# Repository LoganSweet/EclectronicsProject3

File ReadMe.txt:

Olin College of Engineering 
Eclectronics Falls 2017

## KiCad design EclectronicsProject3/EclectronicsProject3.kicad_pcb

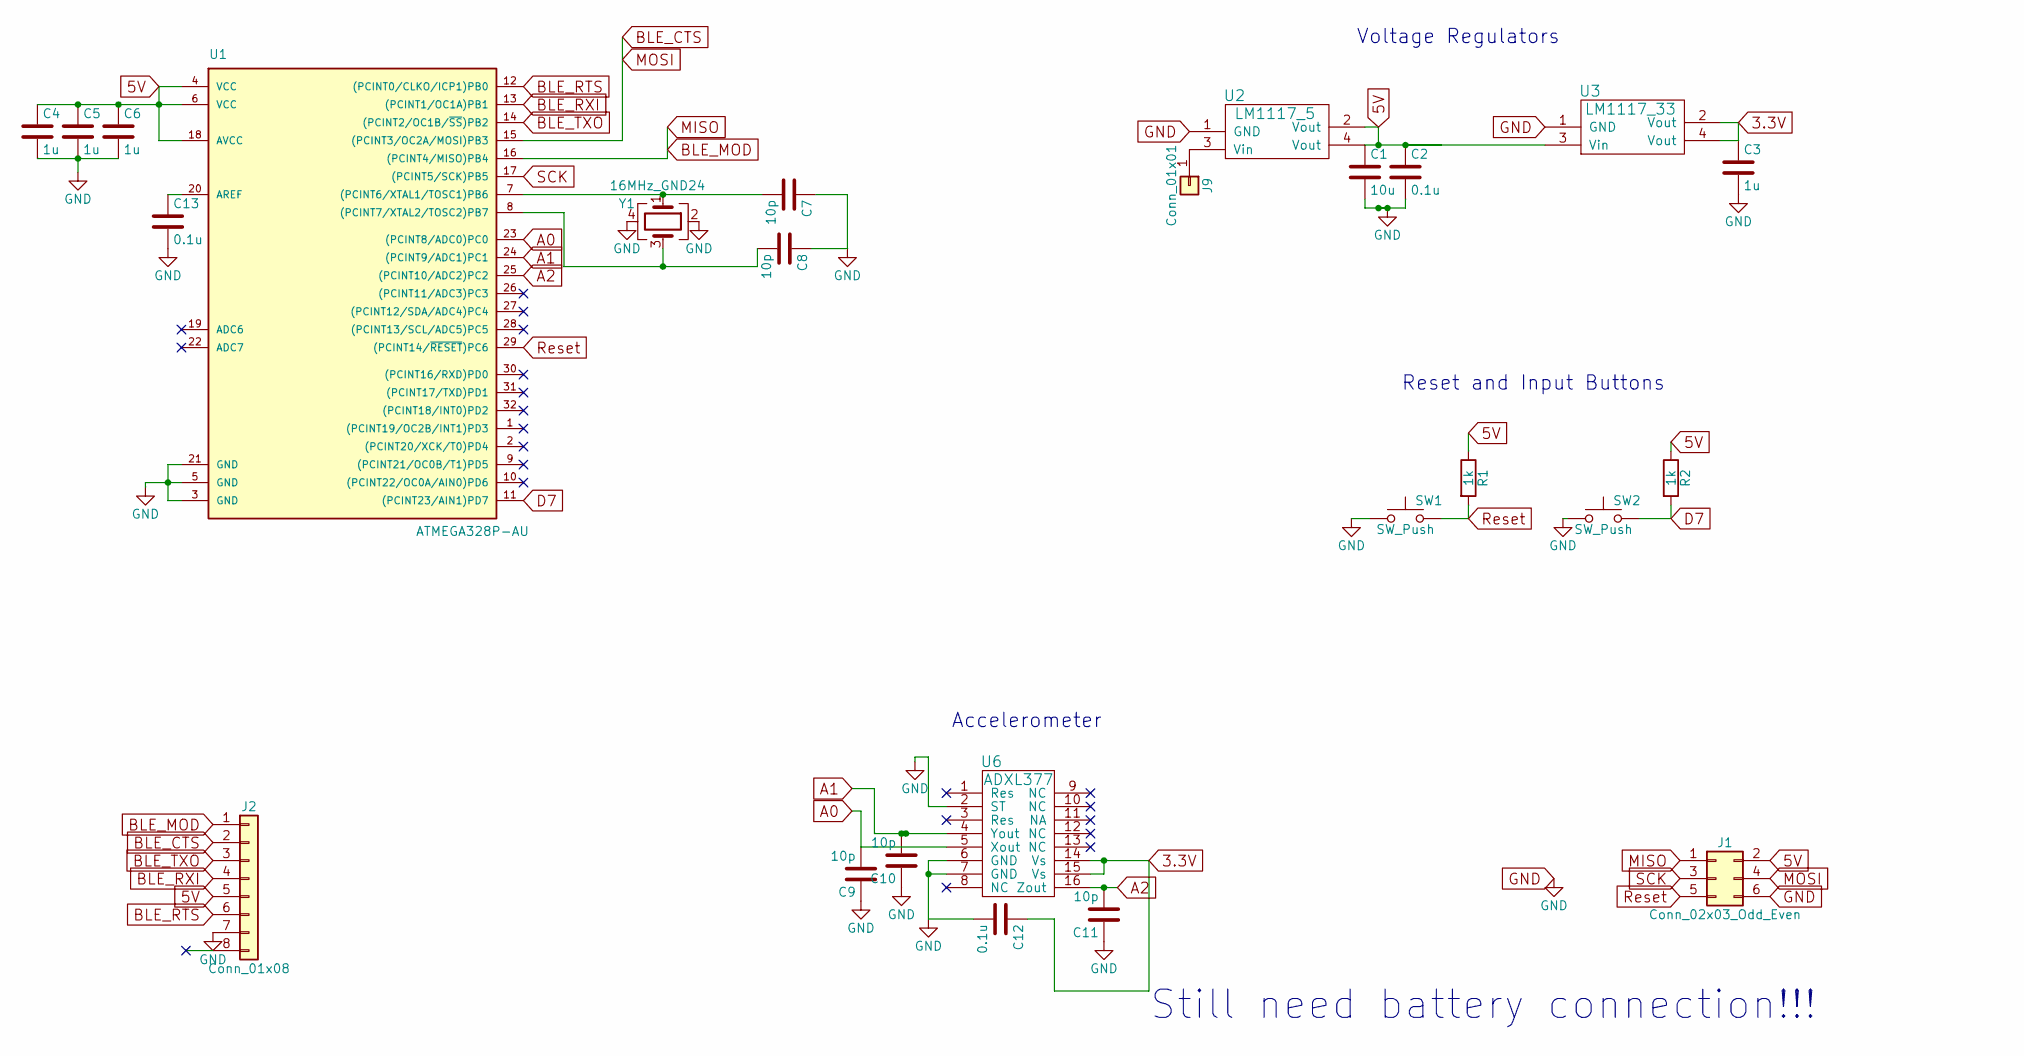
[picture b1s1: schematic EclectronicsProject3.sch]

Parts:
C1: 10u; C_0805
C2, C12, C13: 0.1u; C_0603
C3, C4, C5, C6: 1u; C_0603
C7, C8, C9, C10, C11: 10p; C_0603
J1: Conn_02x03_Odd_Even; Pin_Header_Straight_2x03_Pitch2.54mm
J2: Conn_01x08; Pin_Header_Straight_1x08_Pitch2.54mm
J9: Conn_01x01; Pin_Header_Straight_1x01_Pitch2.54mm
R1, R2: 1k; R_0603
SW1, SW2: SW_Push; SW_SPST_B3U-1000P
U1: ATMEGA328P-AU; TQFP-32_7x7mm_Pitch0.8mm
U2: LM1117_5; SOT-223
U3: LM1117_33; SOT-223
U6: ADXL377; QFN-16-1EP_3x3mm_Pitch0.5mm
Y1: 16MHz_GND24; Crystal_SMD_Abracon_ABM8G-4pin_3.2x2.5mm

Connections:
3.3V: C3.1, C12.1, U3.2 (Vout), U3.4 (Vout), U6.14 (Vs), U6.15 (Vs)
5V: C1.1, C2.1, C4.1, C5.1, C6.1, J1.2, J2.5, R1.1, R2.1, U1.4 (VCC), U1.6 (VCC), U1.18 (AVCC), U2.2 (Vout), U2.4 (Vout), U3.3 (Vin)
A0: C9.2, U1.23 ((PCINT8/ADC0)PC0), U6.5 (Xout)
A1: C10.2, U1.24 ((PCINT9/ADC1)PC1), U6.4 (Yout)
A2: C11.2, U1.25 ((PCINT10/ADC2)PC2), U6.16 (Zout)
BLE_CTS: J1.4, J2.2, U1.15 ((PCINT3/OC2A/MOSI)PB3)
BLE_MOD: J1.1, J2.1, U1.16 ((PCINT4/MISO)PB4)
BLE_RTS: J2.6, U1.12 ((PCINT0/CLKO/ICP1)PB0)
BLE_RXI: J2.4, U1.13 ((PCINT1/OC1A)PB1)
BLE_TXO: J2.3, U1.14 ((PCINT2/OC1B/~SS~)PB2)
D7: R2.2, SW2.2, U1.11 ((PCINT23/AIN1)PD7)
GND: C1.2, C2.2, C3.2, C4.2, C5.2, C6.2, C7.1, C8.1, C9.1, C10.1, C11.1, C12.2, C13.2, J1.6, J2.7, SW1.1, SW2.1, U1.3 (GND), U1.5 (GND), U1.21 (GND), U2.1 (GND), U3.1 (GND), U6.2 (ST), U6.6 (GND), U6.7 (GND), Y1.2, Y1.4
unnamed: C7.2, U1.7 ((PCINT6/XTAL1/TOSC1)PB6), Y1.1
unnamed: C8.2, U1.8 ((PCINT7/XTAL2/TOSC2)PB7), Y1.3
unnamed: C13.1, U1.20 (AREF)
unnamed: J9.1, U2.3 (Vin)
Reset: J1.5, R1.2, SW1.2, U1.29 ((PCINT14/~RESET~)PC6)
SCK: J1.3, U1.17 ((PCINT5/SCK)PB5)

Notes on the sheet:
Accelerometer
Still need battery connection!!!
Reset and Input Buttons
Voltage Regulators

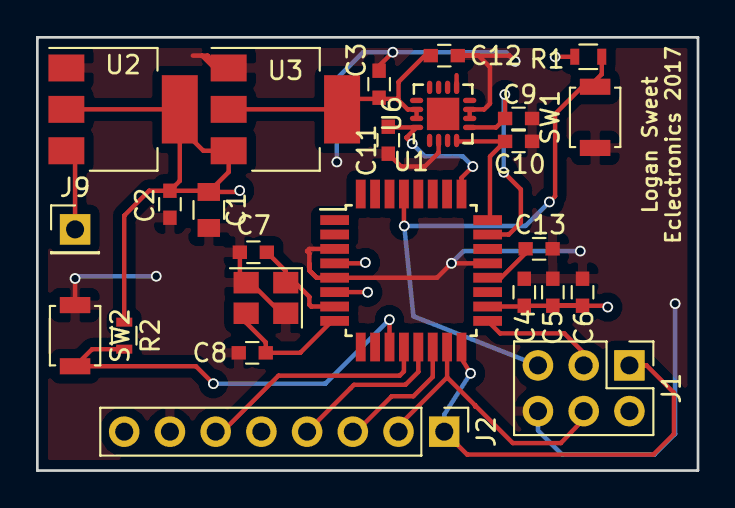
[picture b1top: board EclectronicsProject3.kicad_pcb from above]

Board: 2 copper layers, 36.7 x 24.1 mm, 25 parts (0 on the bottom side), 18 nets.

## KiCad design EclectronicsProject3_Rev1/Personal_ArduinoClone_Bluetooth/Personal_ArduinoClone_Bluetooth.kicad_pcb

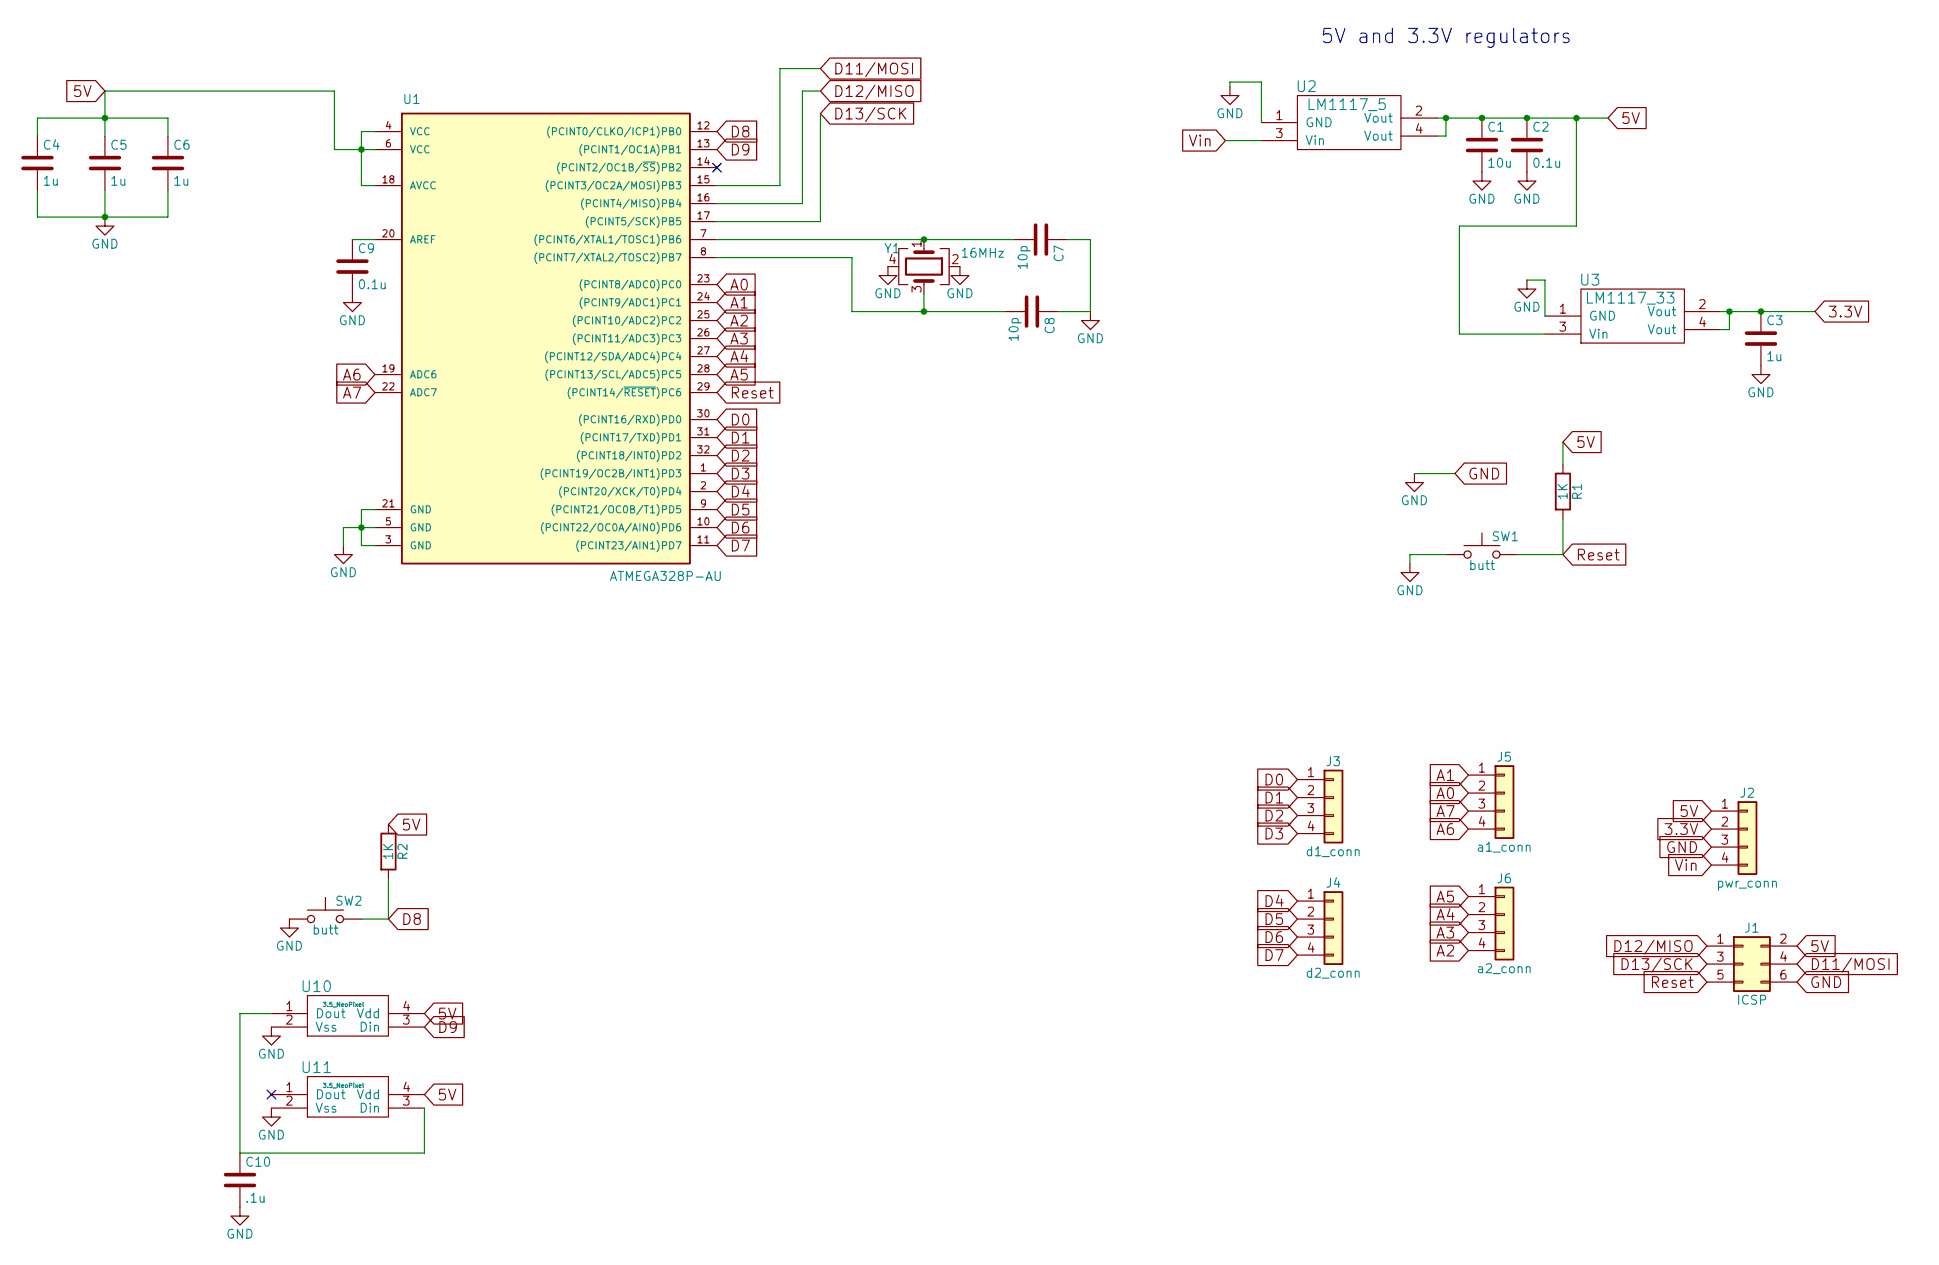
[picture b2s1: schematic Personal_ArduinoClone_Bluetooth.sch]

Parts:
C1: 10u; C_0805
C2, C9: 0.1u; C_0603
C3, C4, C5, C6: 1u; C_0603
C7, C8: 10p; C_0603
C10: .1u; C_0603
J1: ICSP; Pin_Header_Straight_2x03_Pitch2.54mm
J2: pwr_conn; Pin_Header_Straight_1x04_Pitch2.54mm
J3: d1_conn; Pin_Header_Straight_1x04_Pitch2.54mm
J4: d2_conn; Pin_Header_Straight_1x04_Pitch2.54mm
J5: a1_conn; Pin_Header_Straight_1x04_Pitch2.54mm
J6: a2_conn; Pin_Header_Straight_1x04_Pitch2.54mm
R1, R2: 1K; R_0603
SW1, SW2: butt; SW_SPST_B3U-1000P
U1: ATMEGA328P-AU; TQFP-32_7x7mm_Pitch0.8mm
U2: LM1117_5; SOT-223
U3: LM1117_33; SOT-223
U10, U11: 3.5_NeoPixel; LED_Cree-PLCC4_3.2x2.8mm_CCW
Y1: 16MHz; Crystal_SMD_Abracon_ABM8G-4pin_3.2x2.5mm

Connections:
3.3V: C3.1, J2.2, U3.2 (Vout), U3.4 (Vout)
5V: C1.1, C2.1, C4.1, C5.1, C6.1, J1.2, J2.1, R1.1, R2.1, U1.4 (VCC), U1.6 (VCC), U1.18 (AVCC), U2.2 (Vout), U2.4 (Vout), U3.3 (Vin), U10.4 (Vdd), U11.4 (Vdd)
A0: J5.2, U1.23 ((PCINT8/ADC0)PC0)
A1: J5.1, U1.24 ((PCINT9/ADC1)PC1)
A2: J6.4, U1.25 ((PCINT10/ADC2)PC2)
A3: J6.3, U1.26 ((PCINT11/ADC3)PC3)
A4: J6.2, U1.27 ((PCINT12/SDA/ADC4)PC4)
A5: J6.1, U1.28 ((PCINT13/SCL/ADC5)PC5)
A6: J5.4, U1.19 (ADC6)
A7: J5.3, U1.22 (ADC7)
D0: J3.1, U1.30 ((PCINT16/RXD)PD0)
D1: J3.2, U1.31 ((PCINT17/TXD)PD1)
D2: J3.3, U1.32 ((PCINT18/INT0)PD2)
D3: J3.4, U1.1 ((PCINT19/OC2B/INT1)PD3)
D4: J4.1, U1.2 ((PCINT20/XCK/T0)PD4)
D5: J4.2, U1.9 ((PCINT21/OC0B/T1)PD5)
D6: J4.3, U1.10 ((PCINT22/OC0A/AIN0)PD6)
D7: J4.4, U1.11 ((PCINT23/AIN1)PD7)
D8: R2.2, SW2.2, U1.12 ((PCINT0/CLKO/ICP1)PB0)
D9: U1.13 ((PCINT1/OC1A)PB1), U10.3 (Din)
D11/MOSI: J1.4, U1.15 ((PCINT3/OC2A/MOSI)PB3)
D12/MISO: J1.1, U1.16 ((PCINT4/MISO)PB4)
D13/SCK: J1.3, U1.17 ((PCINT5/SCK)PB5)
GND: C1.2, C2.2, C3.2, C4.2, C5.2, C6.2, C7.1, C8.1, C9.2, C10.2, J1.6, J2.3, SW1.1, SW2.1, U1.3 (GND), U1.5 (GND), U1.21 (GND), U2.1 (GND), U3.1 (GND), U10.2 (Vss), U11.2 (Vss), Y1.2, Y1.4
unnamed: C7.2, U1.7 ((PCINT6/XTAL1/TOSC1)PB6), Y1.1
unnamed: C8.2, U1.8 ((PCINT7/XTAL2/TOSC2)PB7), Y1.3
unnamed: C9.1, U1.20 (AREF)
unnamed: C10.1, U10.1 (Dout), U11.3 (Din)
Reset: J1.5, R1.2, SW1.2, U1.29 ((PCINT14/~RESET~)PC6)
Vin: J2.4, U2.3 (Vin)

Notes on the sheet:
5V and 3.3V regulators

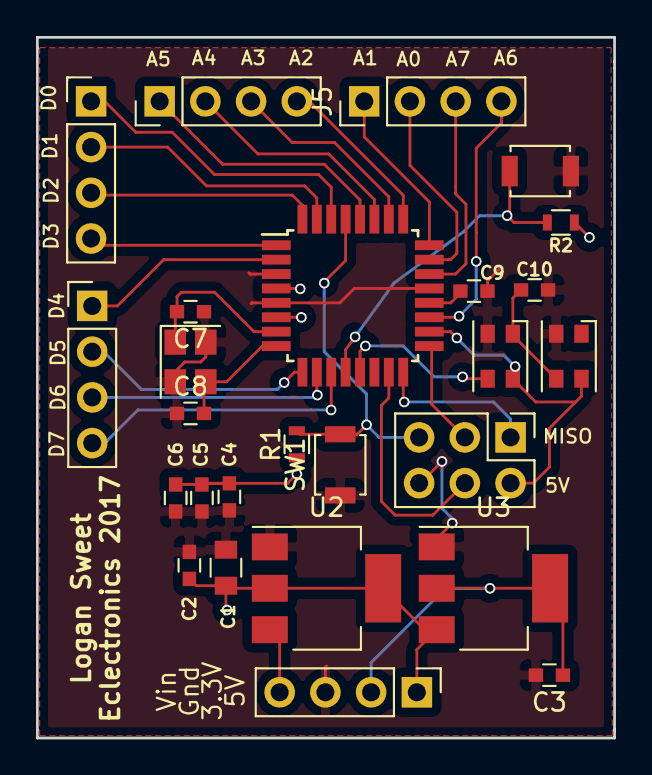
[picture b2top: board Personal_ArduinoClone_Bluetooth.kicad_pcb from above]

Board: 2 copper layers, 32.1 x 38.9 mm, 26 parts (0 on the bottom side), 30 nets.

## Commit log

2017-11-26 adding simple readme since I forgot
2017-11-26 All files added
